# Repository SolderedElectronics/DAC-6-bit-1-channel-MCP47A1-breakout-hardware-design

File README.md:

# DAC 6-bit 1-channel MCP47A1 breakout Hardware Design

## About the Product

|  |
| :----------------------------------------------------------: |
| [Buy DAC 6-bit 1-channel MCP47A1 breakout](https://www.solde.red/333052) |

This device uses MCP47A1 which is a single channel, 6-bit digital to analog converter with I2C compatible serial interface. There’s no integrated EEPROM memory which would allow DAC register and configuration bit values to be saved at powered off.

---

## Repository Contents

This repository contains all design files for DAC 6-bit 1-channel MCP47A1 breakout, organized as follows:

- **`CAD` folder**: Contains KiCAD design files, including:
  - Schematics
  - PCB layout
  - Panel PCB layout
  - Source 3D files in Fusion360, if any
  - All files are sorted by version with a detailed change log.
- **`OUTPUTS` folder**: Includes all production-ready files, such as:
  - Bill of Materials (BOM) and interactive BOM (iBOM)
  - PDF versions of schematics
  - 3D `.step` file of the board
  - 3D-printable models
  - Gerber files for PCB manufacturing
  - Image of the pinout of the board
  - Product image
  - Compliance, legal and generic sales documents

Refer to the `Change Log` in the CAD folder for details about updates between versions.

---

## Learn More About the Product

Beyond the repository, explore the following resources:

### Soldered Verify

The **Soldered Verify** system ensures every board you purchase from Soldered is fully functional. It also provides access to exclusive test data for your product. To get started, find the unique Soldered Verify ID on your product's packaging and enter the ID on the [Soldered Verify page](https://soldered.com/verify/) to access test results and additional product details.

### Soldered Community

Soldered Community is your go-to place for technical support. Our engineers track and answer all questions posted there, and it’s a great space for the maker community. Get answers to your questions and solutions for your challenges at [Soldered Community](https://soldered.com/community).

### solde.red

solde.red is an ultimate URL shortener and information hub. Access it by typing solde.red/ followed by your product SKU, e.g., [solde.red/333000](https://solde.red/333000), to find getting-started guides, datasheets, open-source hardware and software files, certifications, images, pinouts, and more. Read more about the shortener [here](https://solde.red/info/).

---

## Contributing

Contributions are welcome! Here’s how you can get involved:

- Submit pull requests to enhance the design or fix issues.
- Report bugs or problems by opening an issue.

We encourage community collaboration to make this product even better.

---

## About Soldered

[Soldered for Makers](https://soldered.com) specializes in designing and manufacturing electronic products tailored for enthusiasts, ranging from hobbyists to professionals. Our portfolio includes electronic boards, sensors, and actuators that are widely utilized in fields such as microelectronics, mechatronics, robotics, programming, and IoT. Every product we offer is designed in-house and built upon open-source hardware and software platforms. Proudly certified and manufactured within the European Union, our catalog likely includes the product you need for your project.

We complement these products with comprehensive tutorials and manuals, product descriptions, schematics, programming codes, and project examples. Our round-the-clock [customer and technical support](https://soldered.com/community) is available for all our products, irrespective of the sales channel. Soldered’s success and services reflect our maker community’s unwavering [trust](https://www.trustpilot.com/review/soldered.com), for which we are deeply grateful. Join our community and create using Soldered products.

---

## License

All Soldered open-source hardware (OSH) is under The TAPR Open Hardware License. Read more in the LICENSE file located in this repository.

**Disclaimer:**

No warranty - all designs in this repository are distributed in the hope that they will be useful, but without any warranty. They are provided "AS IS", therefore without warranty of any kind, either expressed or implied. The entire quality and performance of what you do with the contents of this repository are your responsibility. In no event Soldered Electronics will be liable for your damages, or losses, including any general, special, incidental, or consequential damage arising out of the use or inability to use the contents of this repository. 

---

## Have fun!

Thank you for your support from your fellow makers at Soldered Electronics.

Happy Making!

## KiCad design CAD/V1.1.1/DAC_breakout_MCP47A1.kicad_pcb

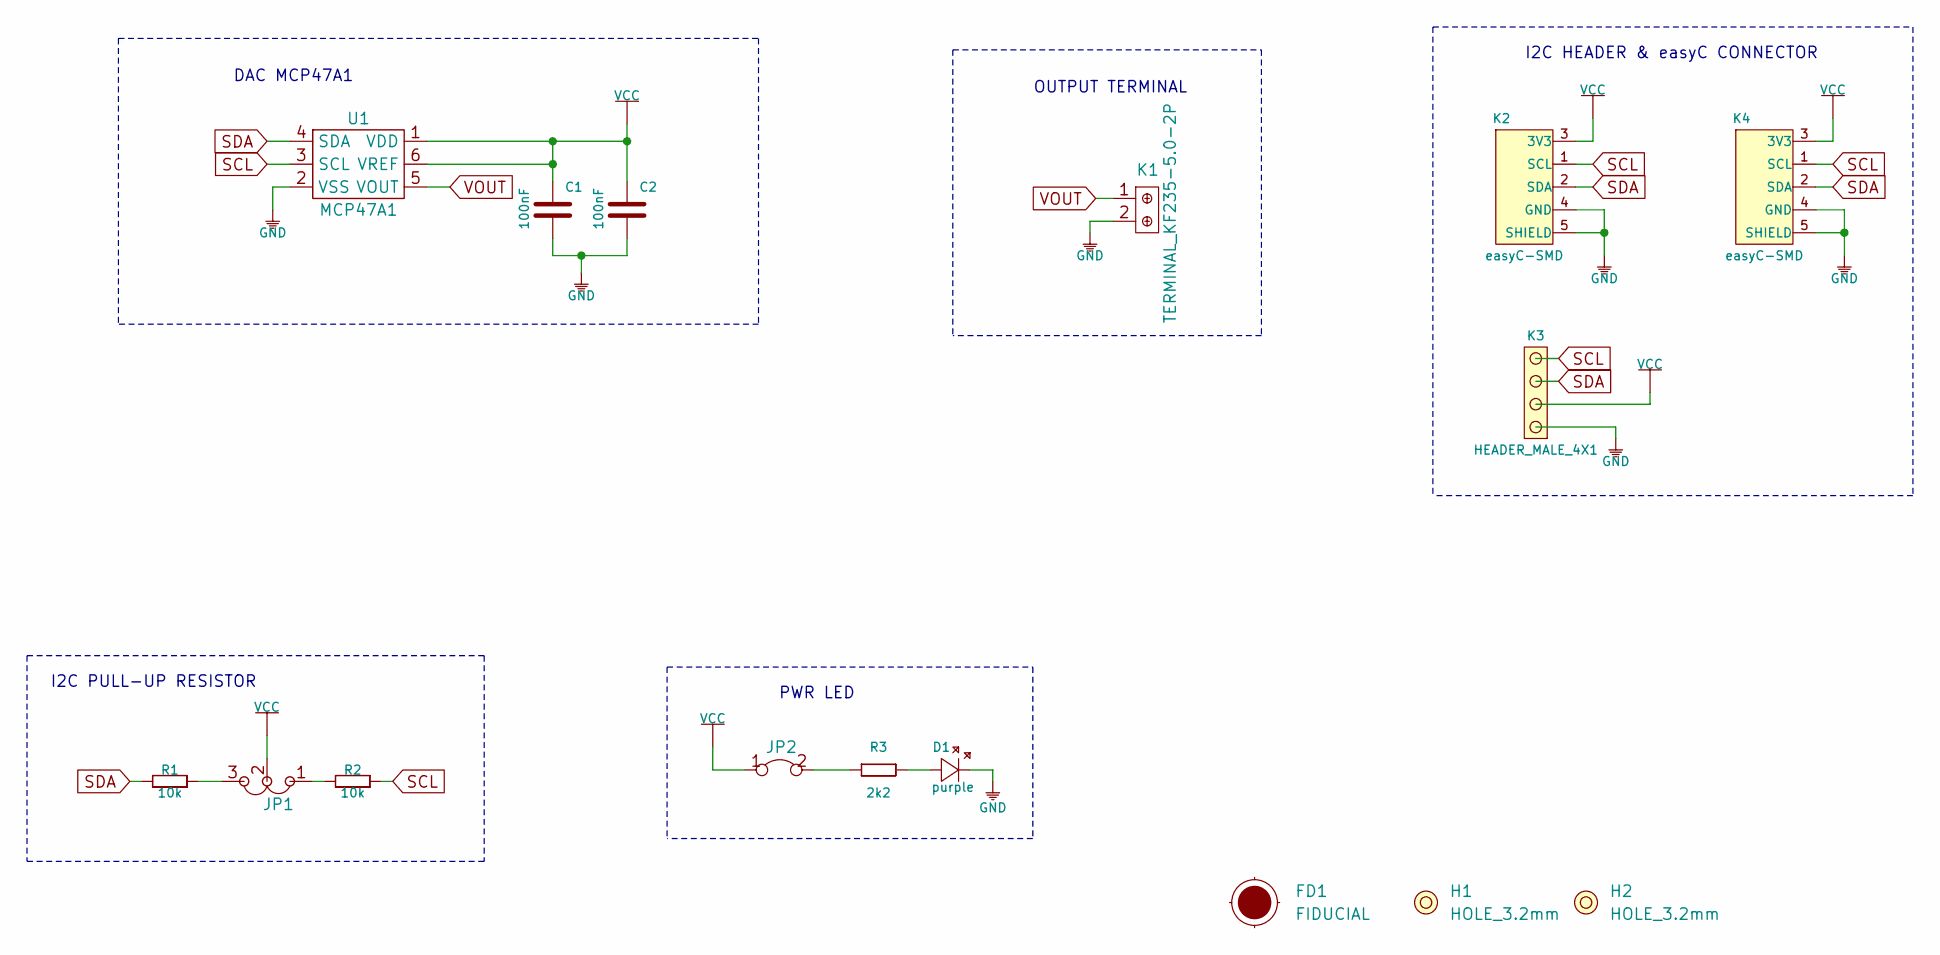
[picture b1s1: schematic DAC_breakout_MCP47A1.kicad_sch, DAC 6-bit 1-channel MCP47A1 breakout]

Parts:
C1, C2: 100nF; 0603C
D1: purple; 0402LED
FD1: FIDUCIAL; FIDUCIAL_23
H1, H2: HOLE_3.2mm
JP1: SMD_JUMPER_3_PAD_TRACE
JP2: SMD-JUMPER-CONNECTED_TRACE_SLODERMASK
K1: TERMINAL_KF235-5.0-2P
K2, K4: easyC-SMD; easyC-connector
K3: HEADER_MALE_4X1
R1, R2: 10k; 0603R
R3: 2k2; 0402R
U1: MCP47A1; MCP47A1-SOT23-6

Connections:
GND: C1.1, C2.1, D1.2 (K), K1.2, K2.4 (GND), K2.5 (SHIELD), K3.1, K4.4 (GND), K4.5 (SHIELD), U1.2 (VSS)
unnamed: D1.1 (A), R3.2
unnamed: JP1.1, R2.2
unnamed: JP1.3, R1.1
unnamed: JP2.2, R3.1
SCL: K2.1 (SCL), K3.4, K4.1 (SCL), R2.1, U1.3 (SCL)
SDA: K2.2 (SDA), K3.3, K4.2 (SDA), R1.2, U1.4 (SDA)
VCC: C1.2, C2.2, JP1.2, JP2.1, K2.3 (3V3), K3.2, K4.3 (3V3), U1.1 (VDD), U1.6 (VREF)
VOUT: K1.1, U1.5 (VOUT)

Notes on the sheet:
OUTPUT TERMINAL
PWR LED
I2C PULL-UP RESISTOR
I2C HEADER & easyC CONNECTOR
DAC MCP47A1

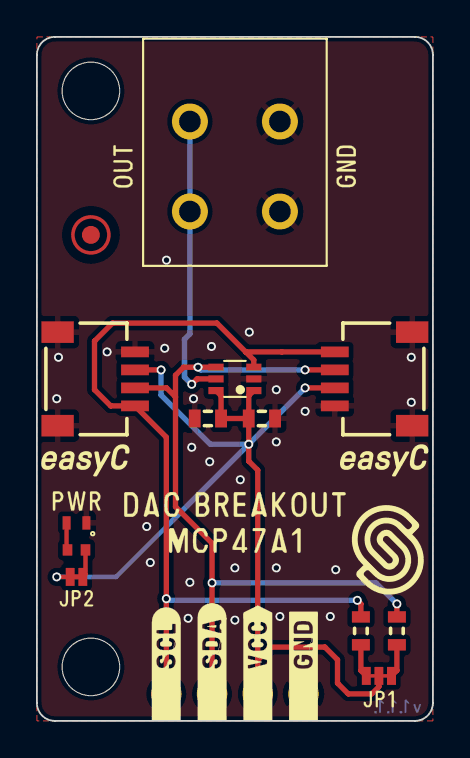
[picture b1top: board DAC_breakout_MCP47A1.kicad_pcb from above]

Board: 2 copper layers, 22.0 x 38.0 mm, 16 parts (1 on the bottom side), 9 nets.

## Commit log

2022-08-06 Updating open source files.
